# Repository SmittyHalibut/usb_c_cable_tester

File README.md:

# USB Cable Tester

Simple board to test various USB cables! (Note the USB standard helps to identify these [USB-C](https://www.usb.org/usb-type-cr-cable-and-connector-specification), cables that are compliant with the standard will have selected pins according to [cable and connector specification release](https://www.usb.org/sites/default/files/USB%20Type-C%202.2%20Release%20202210%20%281%29.zip)). 

Plug in your cable to both sides and see which signals light up!

**FOR CABLE USE ONLY. DO NOT EVER PLUG THIS IN TO A DEVICE, THE PINS ON ONE SIDE ARE ALL SHORTED TOGETHER AND THAT COULD BREAK IT!**

## Board Variants

There are three variants of the board, each living in its own directory with the KiCad
source and ordering instructions. Pick the one that fits how you want to build it:

| Variant | Folder | Best for | Ordering |
|---------|--------|----------|----------|
| **Hand-solder** | [`hand-solder/`](hand-solder/) | DIY builds — through-hole-friendly parts from Digikey/Mouser, easy to solder and rework | [ordering](hand-solder/ORDERING.md) |
| **JLCPCB SMD** | [`jlcpcb-smd/`](jlcpcb-smd/) | Cheapest fully-assembled boards using current JLCPCB stock | [ordering](jlcpcb-smd/ORDERING.md) |
| **JLCPCB vertical** | [`jlcpcb-vertical/`](jlcpcb-vertical/) | Newest design (v3.0) — vertical connectors, through-hole where possible | [ordering](jlcpcb-vertical/ORDERING.md) |

Each folder is a self-contained KiCad project — open the `.kicad_pro` inside it.

## Related Projects!
@coryalder made a neat [3d printed/laser cut case](https://github.com/coryalder/usb-c-tester-case). Check it out! (But make sure it's for the correct version, since components have changed)

[@foorschtbar@chaos.social](https://mastodon.social/@foorschtbar@chaos.social) made a really nice 3D printed case (multicolor). You can [find it here.](https://www.printables.com/model/1003847-usb-cable-tester-multicolor-case)

## License
USB Cable Tester © 2024 by Alvaro Prieto is licensed under CC BY 4.0. To view a copy of this license, visit http://creativecommons.org/licenses/by/4.0/

The v3.0 (vertical) variant includes modifications © 2026 by Mark Smith, Halibut Electronics Inc. Same license applies.

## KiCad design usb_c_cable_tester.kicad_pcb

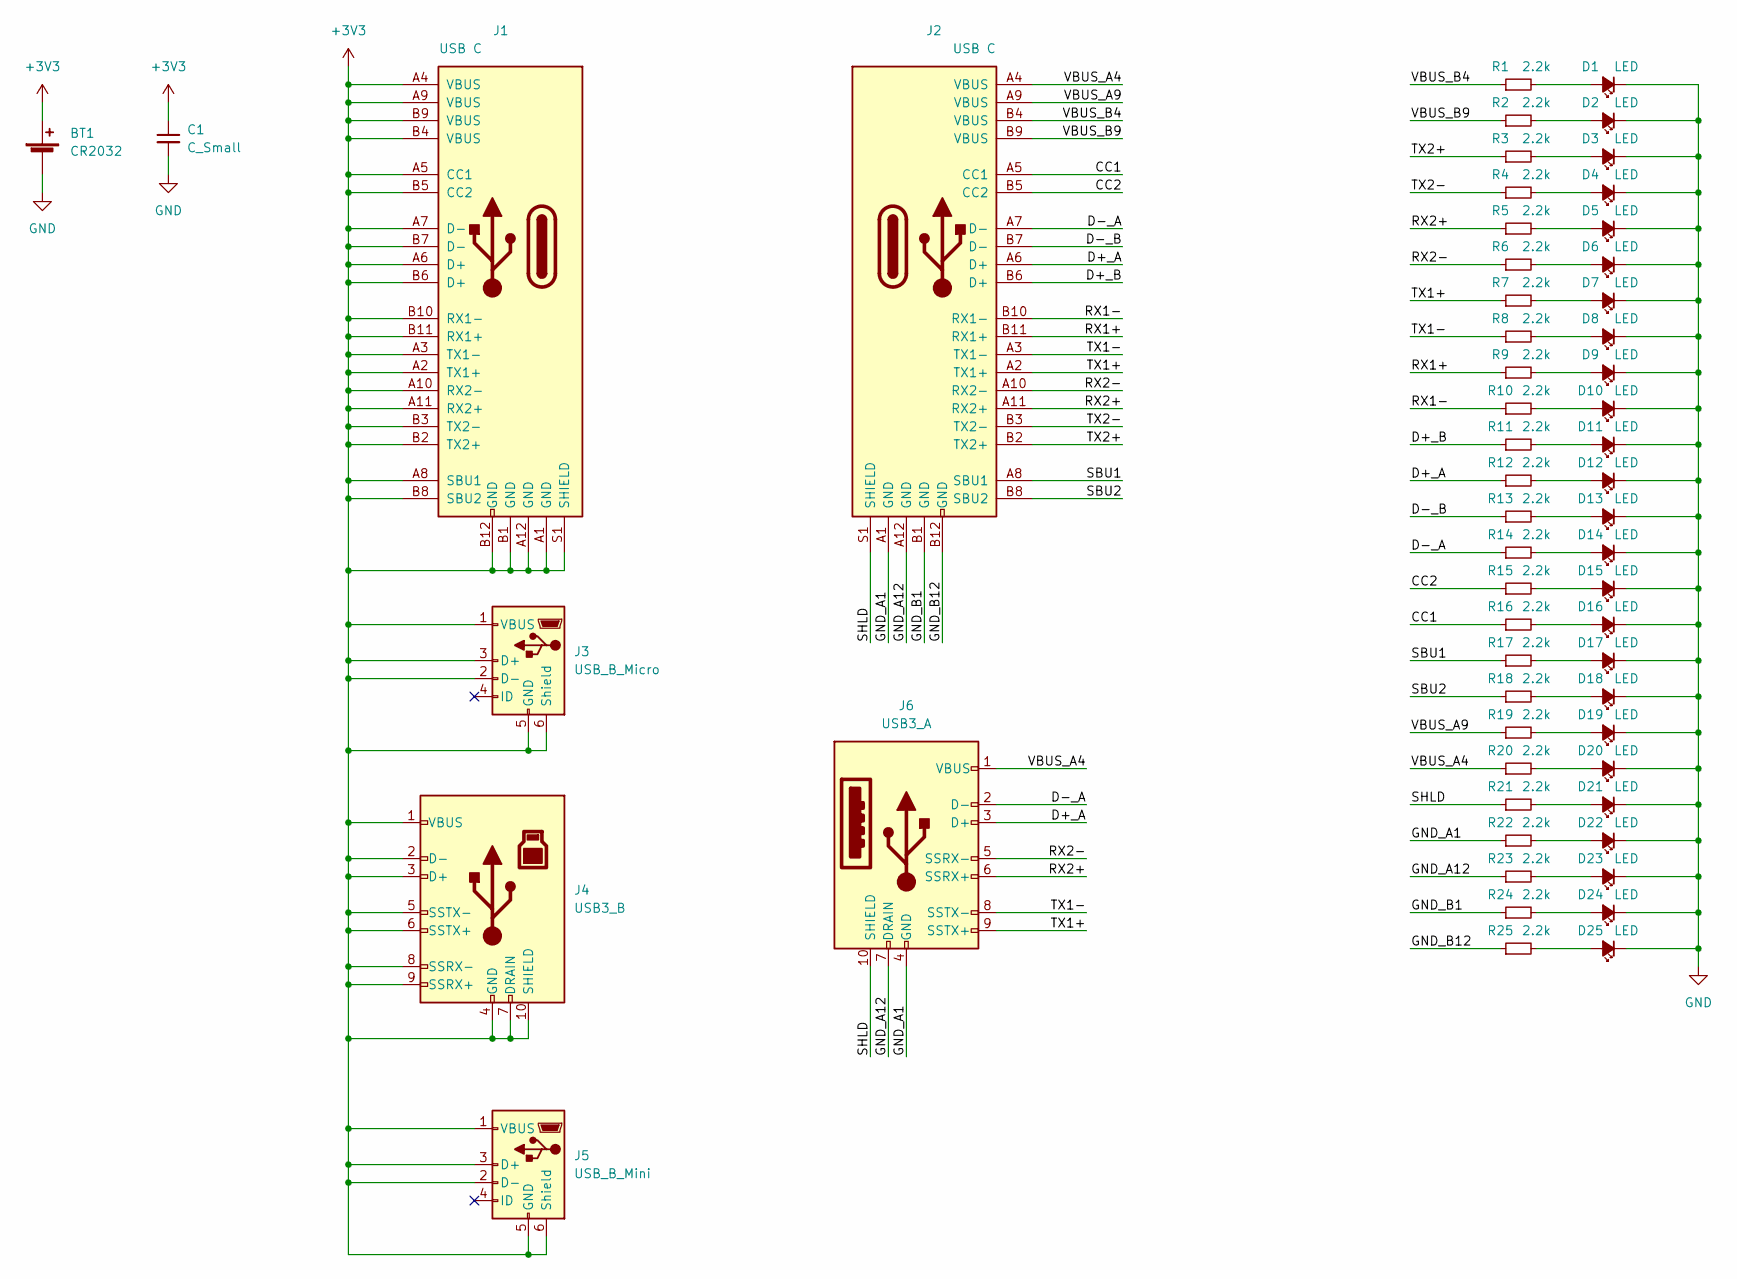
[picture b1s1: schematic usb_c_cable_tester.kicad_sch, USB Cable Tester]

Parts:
BT1: CR2032; BAT-TH_CR2032-BS-6-1; LCSC C7498148
C1: C_Small; C_0805_2012Metric_Pad1.18x1.45mm_HandSolder; LCSC C15850
D1, D2, D3, D4, D5, D6, D7, D8, D9, D10, D11, D12, D13, D14, D15, D16, D17, D18, D19, D20, D21, D22, D23, D24, D25: LED; LED_0603_1608Metric_Pad1.05x0.95mm_HandSolder; LCSC C2286
J1, J2: USB C; USB_C_Receptacle_JAE_DX07S024WJ3R400; LCSC C2840387
J3: USB_B_Micro; USB_Micro-B_Wuerth_614105150721_Vertical; LCSC C456007
J4: USB3_B; USB_B_3.0_C2763106; LCSC C2763106
J5: USB_B_Mini; USB_Mini-B_Tensility_54-00023_Vertical; LCSC C13453
J6: USB3_A; USB_A_3.0_HC-USB3.0-L137-ZP_C19273972; LCSC C381137
R1, R2, R3, R4, R5, R6, R7, R8, R9, R10, R11, R12, R13, R14, R15, R16, R17, R18, R19, R20, R21, R22, R23, R24, R25: 2.2k; R_0603_1608Metric_Pad0.98x0.95mm_HandSolder; LCSC C4190

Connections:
+3V3: BT1.1 (+), C1.1, J1.A1 (GND), J1.A2 (TX1+), J1.A3 (TX1-), J1.A4 (VBUS), J1.A5 (CC1), J1.A6 (D+), J1.A7 (D-), J1.A8 (SBU1), J1.A9 (VBUS), J1.A10 (RX2-), J1.A11 (RX2+), J1.A12 (GND), J1.B1 (GND), J1.B2 (TX2+), J1.B3 (TX2-), J1.B4 (VBUS), J1.B5 (CC2), J1.B6 (D+), J1.B7 (D-), J1.B8 (SBU2), J1.B9 (VBUS), J1.B10 (RX1-), J1.B11 (RX1+), J1.B12 (GND), J1.S1 (SHIELD), J3.1 (VBUS), J3.2 (D-), J3.3 (D+), J3.5 (GND), J3.6 (Shield), J4.1 (VBUS), J4.2 (D-), J4.3 (D+), J4.4 (GND), J4.5 (SSTX-), J4.6 (SSTX+), J4.7 (DRAIN), J4.8 (SSRX-), J4.9 (SSRX+), J4.10 (SHIELD), J5.1 (VBUS), J5.2 (D-), J5.3 (D+), J5.5 (GND), J5.6 (Shield); also elsewhere on the board
/CC1: J2.A5 (CC1), R16.1
/CC2: J2.B5 (CC2), R15.1
/D+_A: J2.A6 (D+), J6.3 (D+), R12.1
/D+_B: J2.B6 (D+), R11.1
/D-_A: J2.A7 (D-), J6.2 (D-), R14.1
/D-_B: J2.B7 (D-), R13.1
/GND_A1: J2.A1 (GND), J6.4 (GND), R22.1
/GND_A12: J2.A12 (GND), J6.7 (DRAIN), R23.1
/GND_B1: J2.B1 (GND), R24.1
/GND_B12: J2.B12 (GND), R25.1
/RX1+: J2.B11 (RX1+), R9.1
/RX1-: J2.B10 (RX1-), R10.1
/RX2+: J2.A11 (RX2+), J6.6 (SSRX+), R5.1
/RX2-: J2.A10 (RX2-), J6.5 (SSRX-), R6.1
/SBU1: J2.A8 (SBU1), R17.1
/SBU2: J2.B8 (SBU2), R18.1
/SHLD: J2.S1 (SHIELD), J6.10 (SHIELD), R21.1
/TX1+: J2.A2 (TX1+), J6.9 (SSTX+), R7.1
/TX1-: J2.A3 (TX1-), J6.8 (SSTX-), R8.1
/TX2+: J2.B2 (TX2+), R3.1
/TX2-: J2.B3 (TX2-), R4.1
/VBUS_A4: J2.A4 (VBUS), J6.1 (VBUS), R20.1
/VBUS_A9: J2.A9 (VBUS), R19.1
/VBUS_B4: J2.B4 (VBUS), R1.1
/VBUS_B9: J2.B9 (VBUS), R2.1
GND: BT1.2 (-), C1.2, D1.1 (K), D2.1 (K), D3.1 (K), D4.1 (K), D5.1 (K), D6.1 (K), D7.1 (K), D8.1 (K), D9.1 (K), D10.1 (K), D11.1 (K), D12.1 (K), D13.1 (K), D14.1 (K), D15.1 (K), D16.1 (K), D17.1 (K), D18.1 (K), D19.1 (K), D20.1 (K), D21.1 (K), D22.1 (K), D23.1 (K), D24.1 (K), D25.1 (K); also elsewhere on the board
unnamed: D1.2 (A), R1.2
unnamed: D2.2 (A), R2.2
unnamed: D3.2 (A), R3.2
unnamed: D4.2 (A), R4.2
unnamed: D5.2 (A), R5.2
unnamed: D6.2 (A), R6.2
unnamed: D7.2 (A), R7.2
unnamed: D8.2 (A), R8.2
unnamed: D9.2 (A), R9.2
unnamed: D10.2 (A), R10.2
unnamed: D11.2 (A), R11.2
unnamed: D12.2 (A), R12.2
unnamed: D13.2 (A), R13.2
unnamed: D14.2 (A), R14.2
unnamed: D15.2 (A), R15.2
unnamed: D16.2 (A), R16.2
unnamed: D17.2 (A), R17.2
unnamed: D18.2 (A), R18.2
unnamed: D19.2 (A), R19.2
unnamed: D20.2 (A), R20.2
unnamed: D21.2 (A), R21.2
unnamed: D22.2 (A), R22.2
unnamed: D23.2 (A), R23.2
unnamed: D24.2 (A), R24.2
unnamed: D25.2 (A), R25.2

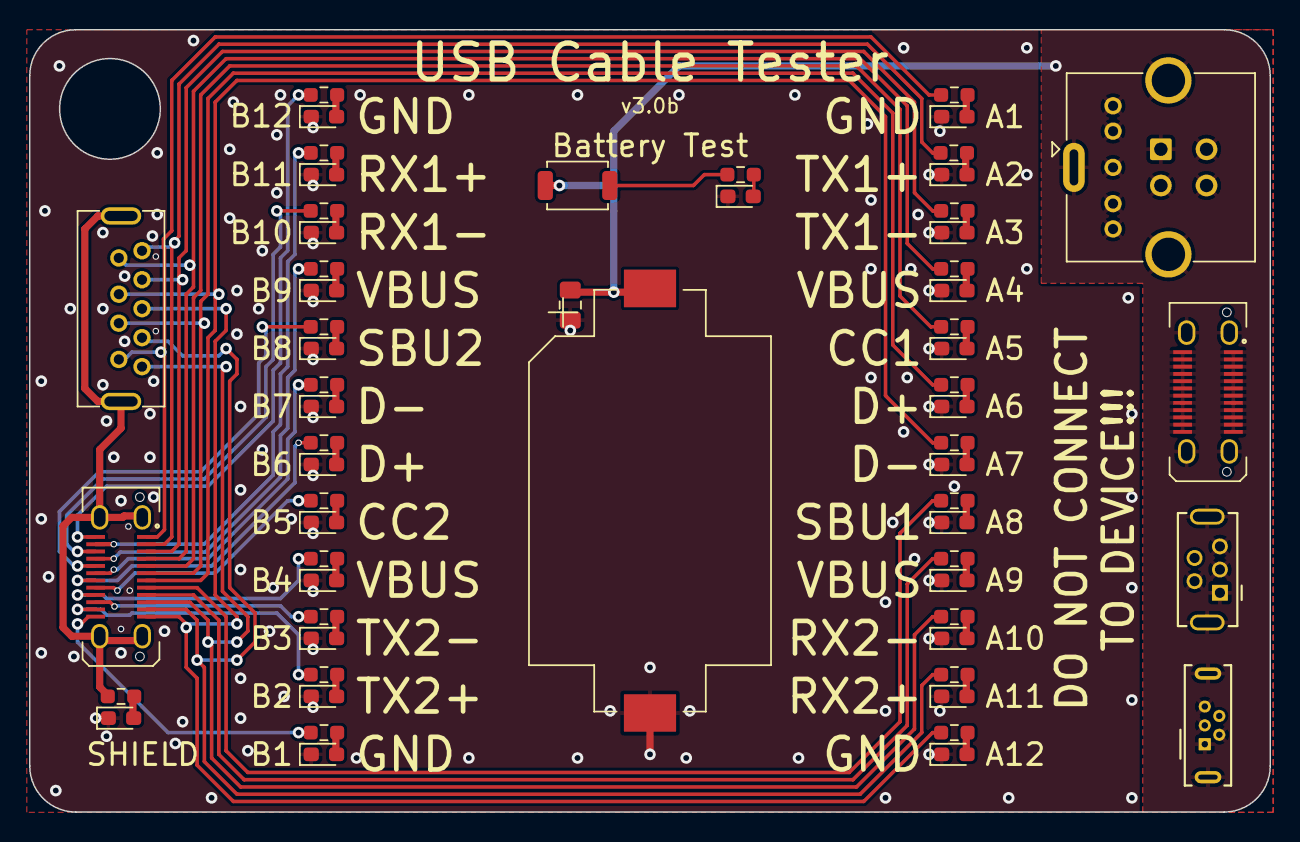
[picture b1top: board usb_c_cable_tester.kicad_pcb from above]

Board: 2 copper layers, 85.6 x 54.0 mm, 61 parts (0 on the bottom side), 54 nets.

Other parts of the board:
D26: LED; LED_0603_1608Metric_Pad1.05x0.95mm_HandSolder
R26: 2.2k; R_0603_1608Metric_Pad0.98x0.95mm_HandSolder
SW1: Battery; SW_SPST_TS-1088-xR020

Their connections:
+3V3: SW1.1; also elsewhere on the board
GND: D26.1 (K); also elsewhere on the board
unnamed: D26.2 (A), R26.2
unnamed: R26.1, SW1.2

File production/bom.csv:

Designator,Footprint,Quantity,Value,LCSC Part #
BT1,BatteryHolder_Keystone_1060_1x2032,1,CR2032,C7498148
C1,0805,1,C_Small,C15850
"D1, D10, D11, D12, D13, D14, D15, D16, D17, D18, D19, D2, D20, D21, D22, D23, D24, D25, D26, D3, D4, D5, D6, D7, D8, D9",0603,26,LED,C2286
"J1, J2",USB_C_Receptacle_JAE_DX07S024WJ3R400,2,USB C,C2840387
J3,USB_Micro-B_Wuerth_614105150721_Vertical,1,USB_B_Micro,C145794
J4,USB_B_3.0_C2763106,1,USB3_B,C2763106
J5,USB_Mini-B_Tensility_54-00023_Vertical,1,USB_B_Mini,C13453
J6,USB_A_3.0_HC-USB3.0-L137-ZP_C19273972,1,USB3_A,C19273972
"R1, R10, R11, R12, R13, R14, R15, R16, R17, R18, R19, R2, R20, R21, R22, R23, R24, R25, R26, R3, R4, R5, R6, R7, R8, R9",0603,26,2.2k,C4190
SW1,SW_SPST_TS-1088-xR020,1,Battery,C720477

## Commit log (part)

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2026-05-26 Moved from https://github.com/SmittyHalibut/usb_c_cable_tester/tree/v2.2-jlcpcb #32
2026-05-26 Adding manufacturing files.
2026-05-26 Removing production file. Didn't work the way I expected.
2026-05-28 Revert "Merging changes for current (2026 May) JLCPCB stock and ordering."
2026-06-17 v3.0. Vertical connectors, through hole where possible. #8, #19, #21, #36
2026-06-17 Oops, missed the USB-A LCSC part number. Fixed. #36
2026-06-21 All three variants coexisting in repo
    Took the Hand-solder, JLCPCB, and JLCPCB vertical variants and put them
    in separate subdirectories.
